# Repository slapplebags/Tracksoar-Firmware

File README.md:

## Tracksoar Firmware
==========
This is a modified version of the [trackduino](https://github.com/trackuino/trackuino) firmware for the [Tracksoar](www.tracksoar.com) hardware.

### Configuring Hardware Version
This branch uses a super basic HAL and as a result must be told what version of hardware it is running on. [Edit the config here](https://github.com/slapplebags/Tracksoar-Firmware/blob/BME280-support/Tracksoar/Firmware/tracksoar/config.h#L30) to have the corect version uncommented. Everything before V1.2 should work as it normally did on the old set of sensors.

#### Build Status

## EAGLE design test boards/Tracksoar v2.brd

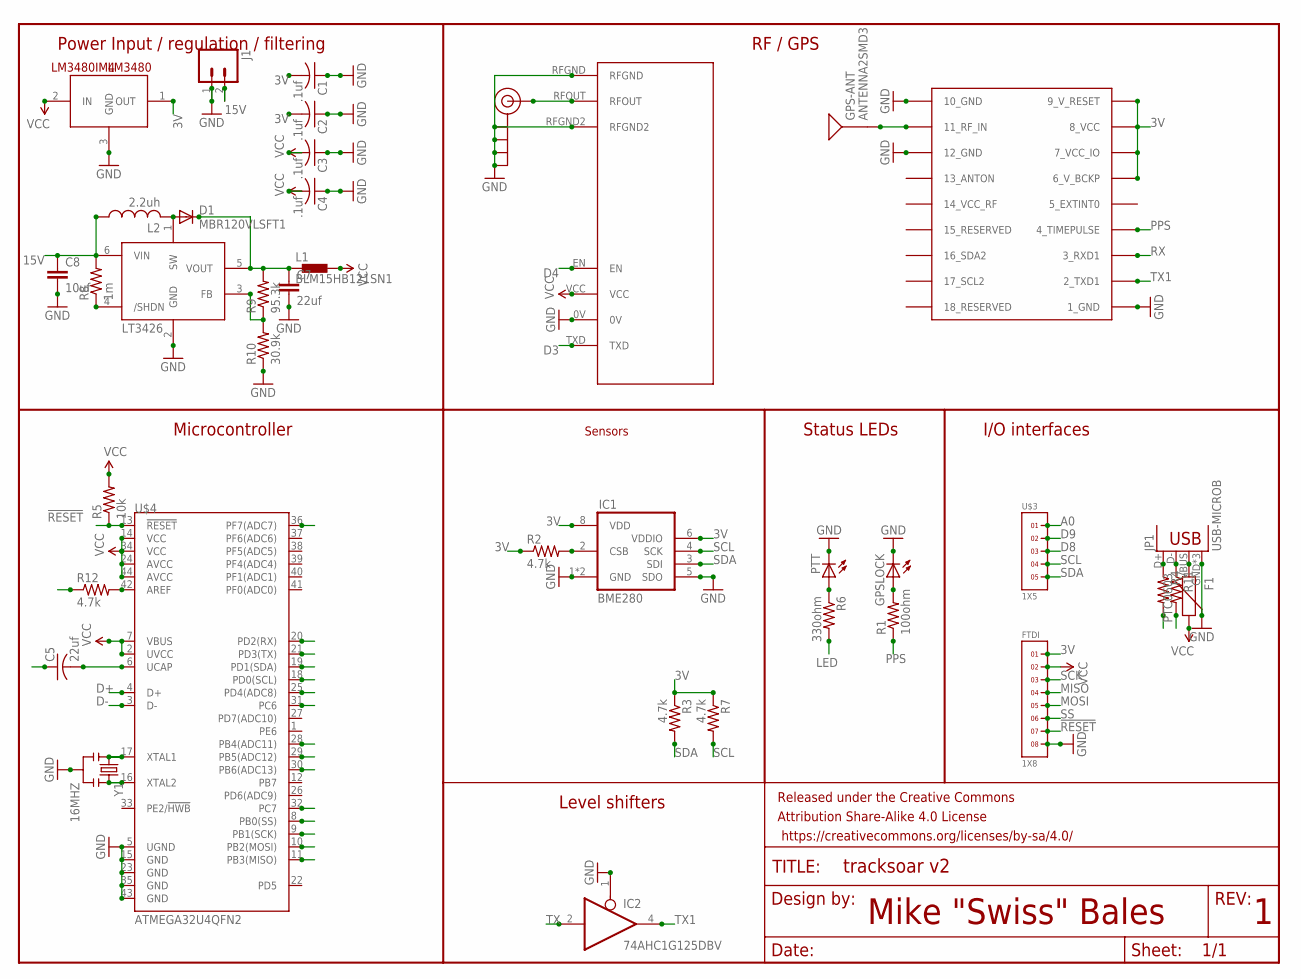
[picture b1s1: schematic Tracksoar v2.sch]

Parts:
C1, C2, C3, C4: .1uf; C0402
C5: 22uf; C0402
C7: 22uf; 0805
C8: 10uf; 0805
D1: MBR120VLSFT1; SOD123
F1: PTC0603; 0603
FRAME1: FRAME-LETTER; CREATIVE_COMMONS
FTDI: 1X8
GPS-ANT: ANTENNA2SMD3; ANTENNA-CHIP4
GPSLOCK: LEDCHIP-LED0603; CHIP-LED0603
IC1: BME280
IC2: 74AHC1G125DBV; SOT23-5
J1: M02JST-PTH-2; JST-2-PTH
J$1: SMA_EDGE; SMA-EDGE
JP1: USB-MICROB
L1: BLM15HB121SN1; 0402
L2: 2.2uh; L1812
LM3480: LM3480IM4; SOT23-3
LT3426: LT3426; SOT23-6
PTT: LEDCHIP-LED0603; CHIP-LED0603
R1: 100ohm; R0402
R2, R3, R7, R12: 4.7k; R0402
R4, R11: R-US_R0402; R0402
R5: 10k; R0402
R6: 330ohm; R0402
R8: 1m; R0402
R9: 95.3k; R0402
R10: 30.9k; R0402
U$1: UBLOX_MAX
U$2: RADIOMETRIX-HX1
U$3: 1X5
U$4: ATMEGA32U4QFN2; QFN-44-NOPAD
Y1: 16MHZ; RESONATOR-SMD

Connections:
3V: C1.2, C2.2, FTDI.1, IC1.6 (VDDIO), IC1.8 (VDD), LM3480.1 (OUT), R2.1, R3.1, R7.1, U$1.6_V_BCKP, U$1.7_VCC_IO, U$1.8_VCC, U$1.9_V_RESET
15V: C8.1, J1.2, L2.1, LT3426.6 (VIN), R8.2, R12.1
!RESET: FTDI.7, R5.1, U$4.13 (!RESET)
A0: U$3.1, U$4.36 (PF7(ADC7))
D3: U$2.TXD, U$4.30 (PB6(ADC13))
D4: U$2.EN, U$4.25 (PD4(ADC8))
D8: U$3.3, U$4.28 (PB4(ADC11))
D9: U$3.2, U$4.29 (PB5(ADC12))
D13: U$4.32 (PC7)
D+: R4.2, U$4.4 (D+)
D-: R11.2, U$4.3 (D-)
GND: C1.1, C2.1, C3.1, C4.1, C5.1, C7.2, C8.2, FTDI.8, GPSLOCK.C, IC1.1 (GND), IC1.5 (SDO), IC1.7 (GND), IC2.1 (OE), IC2.3 (GND), J1.1, J$1.GND@0 (GND), J$1.GND@1 (GND), J$1.GND@2 (GND), J$1.GND@3 (GND), JP1.GND, JP1.MT1 (GND), JP1.MT2 (GND), LM3480.3 (GND), LT3426.2 (GND), PTT.C, R10.1, U$1.1_GND, U$1.10_GND, U$1.12_GND, U$2.0V, U$2.RFGND, U$2.RFGND2, U$4.5 (UGND), U$4.15 (GND), U$4.23 (GND), U$4.35 (GND), U$4.43 (GND), Y1.2
LED: R6.2, U$4.31 (PC6)
MISO: FTDI.4, U$4.11 (PB3(MISO))
MOSI: FTDI.5, U$4.10 (PB2(MOSI))
unnamed: J$1.SIG (SIGNAL), U$2.RFOUT
unnamed: IC1.2 (CSB), R2.2
unnamed: GPSLOCK.A, R1.2
unnamed: GPS-ANT.SIG, U$1.11_RF_IN
unnamed: JP1.D-, R11.1
unnamed: JP1.D+, R4.1
unnamed: D1.A, L2.2, LT3426.1 (SW)
unnamed: LT3426.4 (/SHDN), R8.1
unnamed: LT3426.3 (FB), R9.1, R10.2
unnamed: F1.1, JP1.VBUS
unnamed: R12.2, U$4.42 (AREF)
unnamed: C7.1, D1.C, L1.1, LT3426.5 (VOUT), R9.2
unnamed: C5.2, U$4.6 (UCAP)
unnamed: PTT.A, R6.1
PPS: R1.1, U$1.4_TIMEPULSE
RX: U$1.3_RXD1, U$4.21 (PD3(TX))
SCK: FTDI.3, U$4.9 (PB1(SCK))
SCL: IC1.4 (SCK), R7.2, U$3.4, U$4.18 (PD0(SCL))
SDA: IC1.3 (SDI), R3.2, U$3.5, U$4.19 (PD1(SDA))
SS: FTDI.6, U$4.8 (PB0(SS))
TX: IC2.2 (I), U$4.20 (PD2(RX))
TX1: IC2.4 (O), U$1.2_TXD1
VCC: C3.2, C4.2, F1.2, FTDI.2, IC2.5 (VCC), L1.2, LM3480.2 (IN), R5.2, U$2.VCC, U$4.2 (UVCC), U$4.7 (VBUS), U$4.14 (VCC), U$4.24 (AVCC), U$4.34 (VCC), U$4.44 (AVCC)
XTAL1: U$4.17 (XTAL1), Y1.1
XTAL2: U$4.16 (XTAL2), Y1.3

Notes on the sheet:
Mike "Swiss" Bales
Power Input / regulation / filtering
RF / GPS
Microcontroller
Level shifters
Status LEDs
I/O interfaces
Sensors

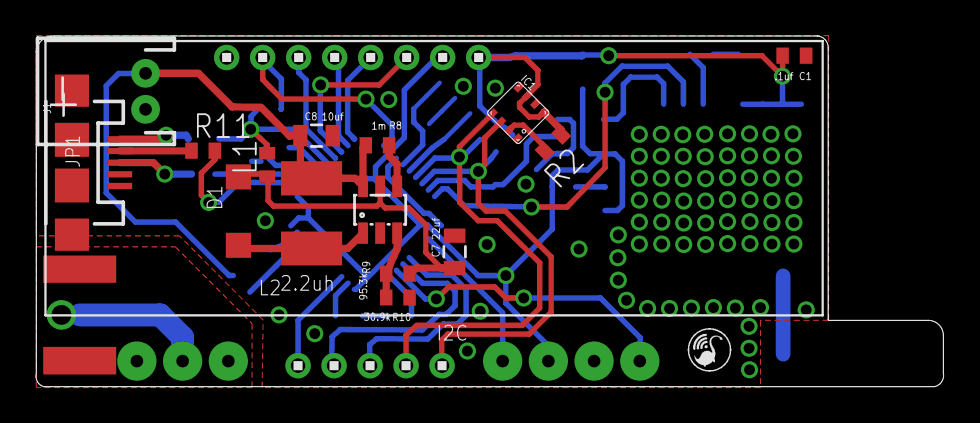
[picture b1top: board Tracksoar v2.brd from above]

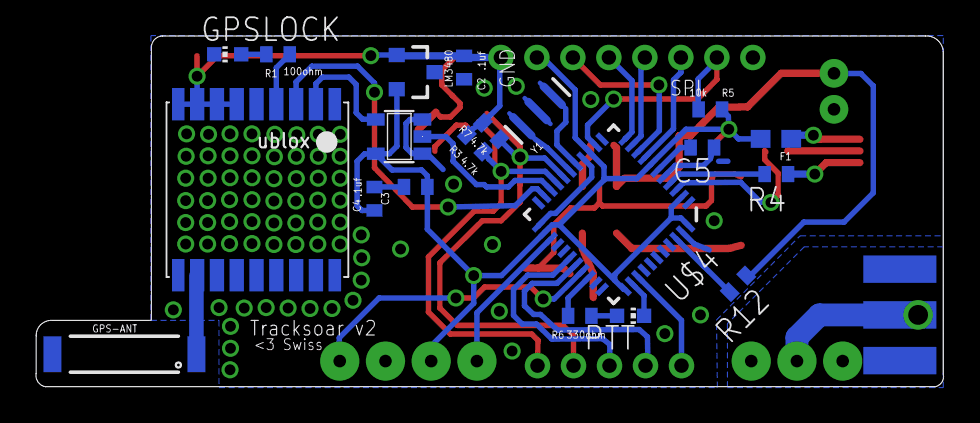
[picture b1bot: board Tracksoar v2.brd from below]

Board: 2 copper layers, 50.4 x 19.5 mm, 40 parts (21 on the bottom side), 39 nets.

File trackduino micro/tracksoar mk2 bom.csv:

"Part";"Value";"Device";"Package";"Description";"MPN";"OC_FARNELL";"OC_NEWARK";"PACKAGE";"PROD_ID";"SUPPLIER";"VALUE";
"BMP180";"BMP180";"BMP180";"BMP180";"BOSCH BMP180 DIGITAL BAROMETRIC PRESSURE SENSOR";"";"";"";"";"";"";"";
"C1";".1uf";"CAP0805";"0805";"Capacitor";"";"";"";"";"";"";"";
"C2";".1uf";"CAP0805";"0805";"Capacitor";"";"";"";"";"";"";"";
"C3";".1uf";"CAP0805";"0805";"Capacitor";"";"";"";"";"";"";"";
"C4";".1uf";"CAP0805";"0805";"Capacitor";"";"";"";"";"";"";"";
"C5";".1uf";"CAP0805";"0805";"Capacitor";"";"";"";"";"";"";"";
"C7";"22uf";"CAP0805";"0805";"Capacitor";"";"";"";"";"";"";"";
"C8";"10uf";"CAP0805";"0805";"Capacitor";"";"";"";"";"";"";"";
"C9";"100uf";"C-USC1206";"C1206";"CAPACITOR, American symbol";"";"";"";"";"";"";"";
"D1";"MBR120VLSFT1";"DIODE-SOD123";"SOD123";"DIODE";"";"";"";"";"";"";"";
"FRAME1";"FRAME-LETTER";"FRAME-LETTER";"CREATIVE_COMMONS";"Schematic Frame";"";"";"";"";"";"";"";
"FTDI";"";"M06NO_SILK_FEMALE_PTH";"1X06_NO_SILK";"Header 6";"";"";"";"";"CONN-08437";"";"";
"IC2";"74AHC1G125DBV";"74AHC1G125DBV";"SOT23-5";"Single Bus Buffer Gate with 3-State Output";"";"";"";"";"";"";"";
"J$1";"SMA_EDGE";"SMA_EDGE";"SMA-EDGE";"SMA Antenna Connector";"";"";"";"";"";"";"";
"JP1";"M02JST-PTH-VERT";"M02JST-PTH-VERT";"JST-2-PTH-VERT";"Standard 2-pin 0.1" header. Use with";"";"";"";"";"";"";"";
"L2";"2.2uh";"L-USL1812";"L1812";"INDUCTOR, American symbol";"";"";"";"";"";"";"";
"LED1";"";"LEDCHIP-LED0805";"CHIP-LED0805";"LED";"";"";"";"";"";"";"";
"LM3480";"LM3480IM4";"LM3480IM4";"SOT23-3";"Small package linear regulator";"";"";"";"";"";"";"";
"LT3426";"LT3426";"LT3426";"SOT23-6";"LT3426";"";"";"";"";"";"";"";
"PTT";"";"LEDCHIP-LED0805";"CHIP-LED0805";"LED";"";"";"";"";"";"";"";
"R1";"100ohm";"RESISTOR0805-RES";"0805";"Resistor";"";"";"";"";"";"";"";
"R3";"4.7k";"RESISTOR0805-RES";"0805";"Resistor";"";"";"";"";"";"";"";
"R5";"10k";"RESISTOR0805-RES";"0805";"Resistor";"";"";"";"";"";"";"";
"R6";"330ohm";"RESISTOR0805-RES";"0805";"Resistor";"";"";"";"";"";"";"";
"R7";"4.7k";"RESISTOR0805-RES";"0805";"Resistor";"";"";"";"";"";"";"";
"R8";"1m";"RESISTOR0805-RES";"0805";"Resistor";"";"";"";"";"";"";"";
"R9";"95.3k";"RESISTOR0805-RES";"0805";"Resistor";"";"";"";"";"";"";"";
"R10";"30.9k";"RESISTOR0805-RES";"0805";"Resistor";"";"";"";"";"";"";"";
"RX";"RX";"M02JST-PTH-VERT";"JST-2-PTH-VERT";"Standard 2-pin 0.1" header. Use with";"";"";"";"";"";"";"";
"SHT21";"SHT21";"SHT21";"DFN300X300X110-7N";"SENSOR, HUMIDITY & TEMP";"SHT21";"1855468";"20T1172";"DFN-6";"";"SENSIRION";"";
"SPI";"";"M04JST-PTH-VERT";"JST-4-PTH-VERT";"Header 4";"";"";"";"";"";"";"";
"SW1";"SPST_TACT-KMR2";"SPST_TACT-KMR2";"KMR2";"SMT 6mm switch, EVQQ2 series";"";"";"";"";"";"";"";
"TX";"TX";"M02JST-PTH-VERT";"JST-2-PTH-VERT";"Standard 2-pin 0.1" header. Use with";"";"";"";"";"";"";"";
"TX1";"TX";"M02JST-PTH-VERT";"JST-2-PTH-VERT";"Standard 2-pin 0.1" header. Use with";"";"";"";"";"";"";"";
"U$1";"UBLOX_MAX";"UBLOX_MAX";"UBLOX_MAX";"UBLOX MAX";"";"";"";"";"";"";"";
"U$2";"RADIOMETRIX-HX1";"RADIOMETRIX-HX1";"RADIOMETRIX-HX1";"";"";"";"";"";"";"";"";
"U$3";"ANTENNA2SMD3";"ANTENNA2SMD3";"ANTENNA-CHIP4";"Chip antenna";"";"";"";"";"";"";"";
"U1";"ATMEGA168MLF";"ATMEGA168MLF";"MLF32";"Atmel 32-pin 8-bit micro, 16k flash.";"";"";"";"";"";"";"";
"Y1";"16MHZ";"RESONATOR16MHZ";"RESONATOR-SMD";"Resonator";"";"";"";"";"XTAL-08900";"";"16MHZ";

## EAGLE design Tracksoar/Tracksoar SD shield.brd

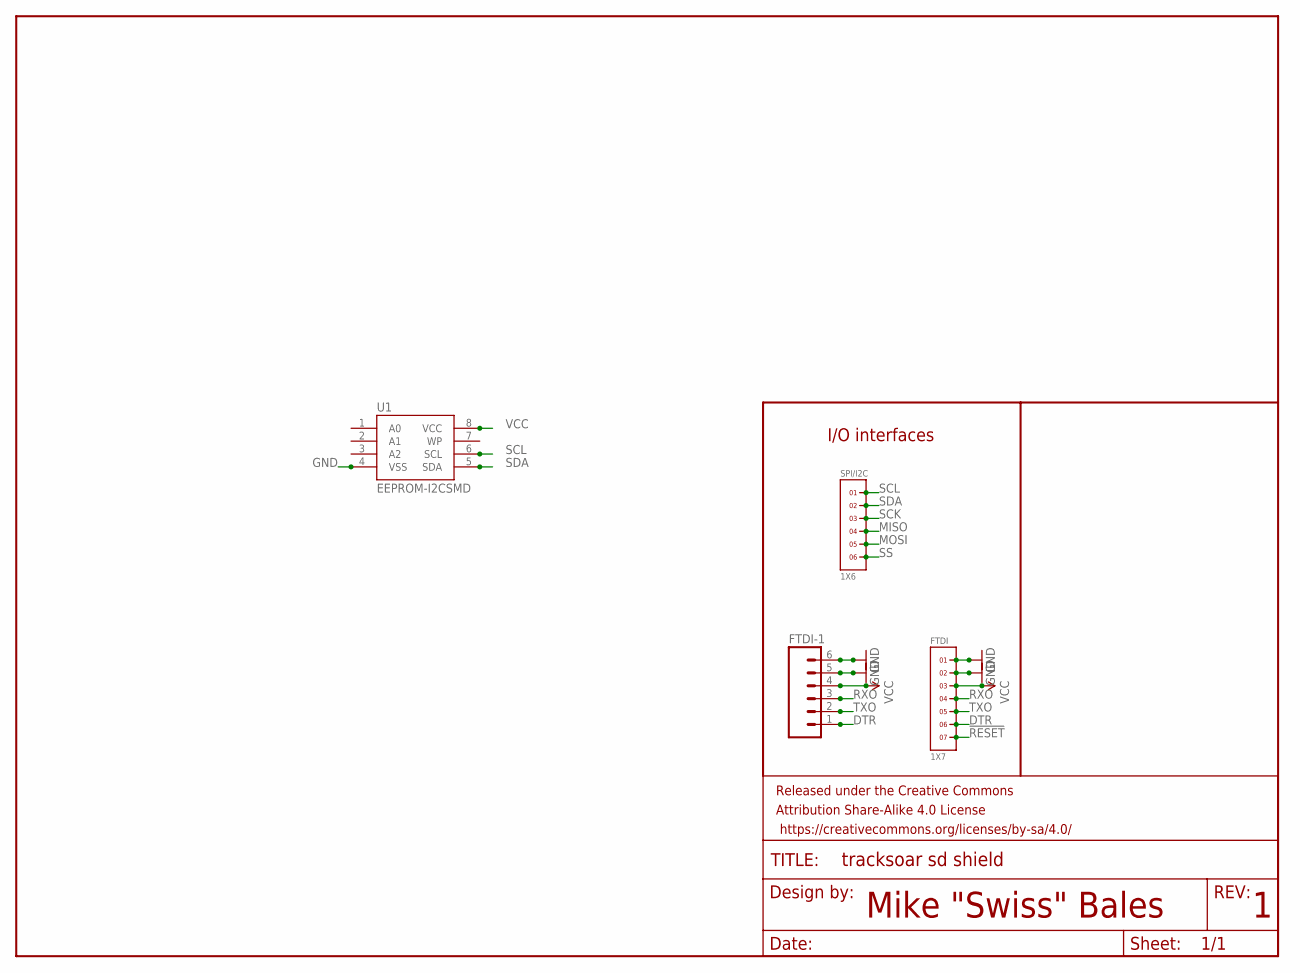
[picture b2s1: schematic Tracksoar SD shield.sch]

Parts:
FRAME1: FRAME-LETTER; CREATIVE_COMMONS
FTDI: 1X7
FTDI-1: M06LOCK_LONGPADS; 1X06_LOCK_LONGPADS
SPI/I2C: 1X6
U1: EEPROM-I2CSMD; SO08

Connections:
!RESET: FTDI.7
DTR: FTDI.6, FTDI-1.1
GND: FTDI.1, FTDI.2, FTDI-1.5, FTDI-1.6, U1.4 (VSS)
MISO: SPI/I2C.4
MOSI: SPI/I2C.5
RXO: FTDI.4, FTDI-1.3
SCK: SPI/I2C.3
SCL: SPI/I2C.1, U1.6 (SCL)
SDA: SPI/I2C.2, U1.5 (SDA)
SS: SPI/I2C.6
TXO: FTDI.5, FTDI-1.2
VCC: FTDI.3, FTDI-1.4, U1.8 (VCC)

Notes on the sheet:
Mike "Swiss" Bales
I/O interfaces

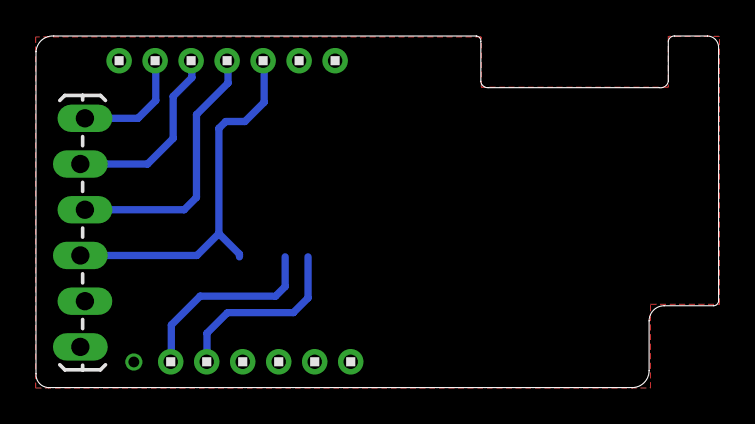
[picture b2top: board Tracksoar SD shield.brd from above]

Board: 2 copper layers, 37.9 x 19.5 mm, 5 parts (1 on the bottom side), 7 nets.

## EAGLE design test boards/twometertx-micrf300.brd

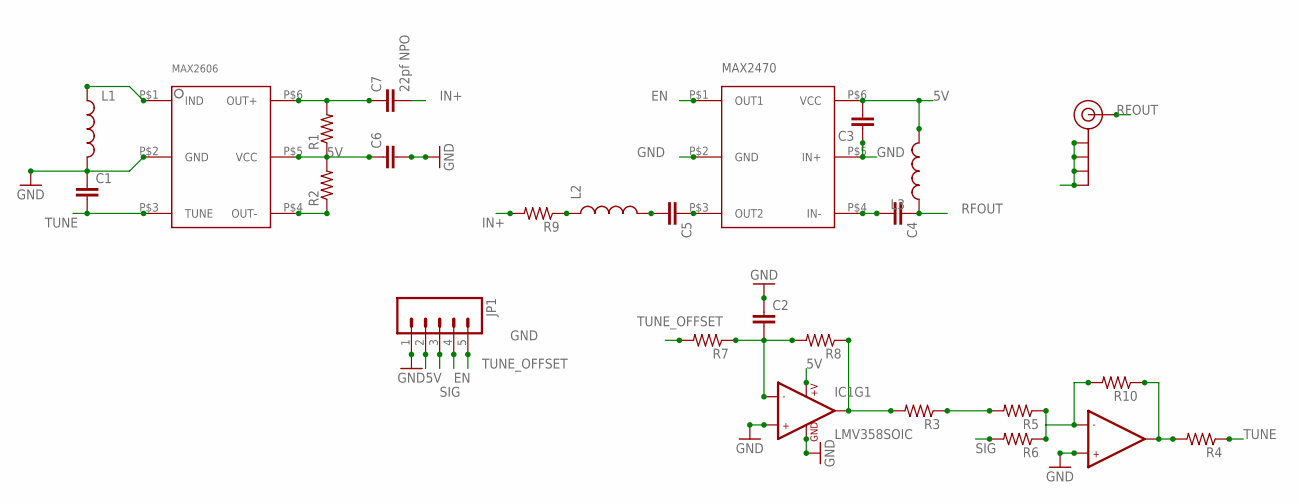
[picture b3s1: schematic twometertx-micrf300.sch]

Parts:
C1, C2, C3, C4, C5, C6: CAP0805; 0805
C7: 22pf NPO; 0805
IC1: LMV358SOIC; SO08
J$1: SMA_EDGE; SMA-EDGE
JP1: M05PTH_LONGPADS; 1X05_LONGPADS
L1, L2, L3: INDUCTOR0805; 0805
R1, R2, R3, R4, R5, R6, R7, R8, R9, R10: RESISTOR0805-RES; 0805
U$1: MAX2606
U$2: MAX2470

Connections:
5V: C3.2, C6.1, IC1.8 (+V), JP1.2, L3.2, R1.1, R2.2, U$1.P$5 (VCC), U$2.P$6 (VCC)
EN: JP1.4, U$2.P$1 (OUT1)
GND: C1.1, C2.1, C3.1, C4.2, C6.2, IC1.3 (+IN1), IC1.4 (GND), IC1.5 (+IN2), J$1.GND@0 (GND), J$1.GND@1 (GND), J$1.GND@2 (GND), J$1.GND@3 (GND), JP1.1, L1.2, U$1.P$2 (GND), U$2.P$2 (GND), U$2.P$4 (IN-), U$2.P$5 (IN+)
IN+: C7.2, R9.2
unnamed: C5.1, U$2.P$3 (OUT2)
unnamed: L1.1, U$1.P$1 (IND)
unnamed: C2.2, IC1.2 (-IN1), R7.1, R8.2
unnamed: C5.2, L2.2
unnamed: R3.1, R5.2
unnamed: IC1.7 (OUT2), R4.2, R10.1
unnamed: IC1.6 (-IN2), R5.1, R6.1, R10.2
unnamed: L2.1, R9.1
unnamed: C7.1, R1.2, U$1.P$6 (OUT+)
unnamed: IC1.1 (OUT1), R3.2, R8.1
RFOUT: C4.1, J$1.SIG (SIGNAL), L3.1
SIG: JP1.3, R6.2
THING2: R2.1, U$1.P$4 (OUT-)
TUNE: C1.2, R4.1, U$1.P$3 (TUNE)
TUNE_OFFSET: JP1.5, R7.2

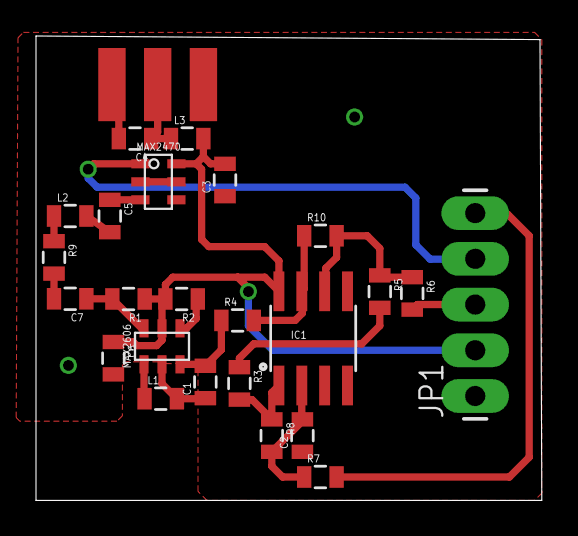
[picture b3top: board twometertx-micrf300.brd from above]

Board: 2 copper layers, 28.1 x 25.8 mm, 25 parts (0 on the bottom side), 19 nets.

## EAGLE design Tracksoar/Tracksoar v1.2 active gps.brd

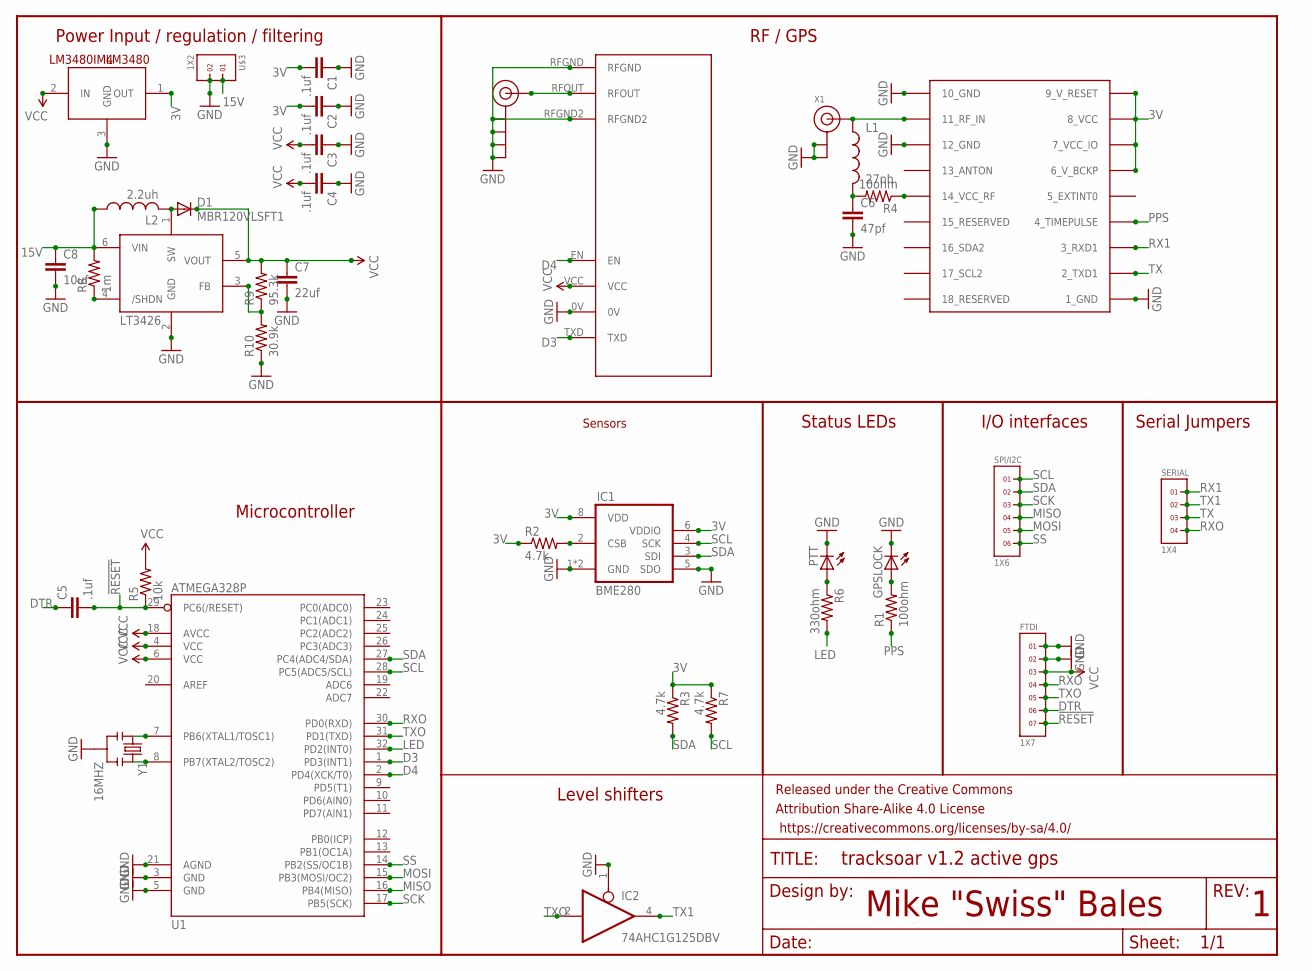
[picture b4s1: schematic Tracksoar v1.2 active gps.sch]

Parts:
C1, C2, C3, C4, C5: .1uf; 0805
C6: 47pf; 0805
C7: 22uf; 0805
C8: 10uf; 0805
D1: MBR120VLSFT1; SOD123
FRAME1: FRAME-LETTER; CREATIVE_COMMONS
FTDI: 1X7
GPSLOCK: LEDCHIP-LED0805; CHIP-LED0805
IC1: BME280
IC2: 74AHC1G125DBV; SOT23-5
J$1: SMA_EDGE; SMA-EDGE
L1: 27nh; 0805
L2: 2.2uh; L1812
LM3480: LM3480IM4; SOT23-3
LT3426: LT3426; SOT23-6
PTT: LEDCHIP-LED0805; CHIP-LED0805
R1: 100ohm; 0805
R2, R3, R7: 4.7k; 0805
R4: 10ohm; 0805
R5: 10k; 0805
R6: 330ohm; 0805
R8: 1m; 0805
R9: 95.3k; 0805
R10: 30.9k; 0805
SERIAL: 1X4
SPI/I2C: 1X6
U1: ATMEGA328P; MLF32
U$1: UBLOX_MAX
U$2: RADIOMETRIX-HX1
U$3: 1X2
X1: ANTENNA_U.FL; U.FL
Y1: 16MHZ; RESONATOR-SMD

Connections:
3V: C1.2, C2.2, IC1.6 (VDDIO), IC1.8 (VDD), LM3480.1 (OUT), R2.1, R3.1, R7.1, U$1.6_V_BCKP, U$1.7_VCC_IO, U$1.8_VCC, U$1.9_V_RESET
15V: C8.1, L2.1, LT3426.6 (VIN), R8.2, U$3.1
!RESET: C5.2, FTDI.7, R5.1, U1.29 (PC6(/RESET))
D3: U1.1 (PD3(INT1)), U$2.TXD
D4: U1.2 (PD4(XCK/T0)), U$2.EN
DTR: C5.1, FTDI.6
GND: C1.1, C2.1, C3.1, C4.1, C6.2, C7.2, C8.2, FTDI.1, FTDI.2, GPSLOCK.C, IC1.1 (GND), IC1.5 (SDO), IC1.7 (GND), IC2.1 (OE), IC2.3 (GND), J$1.GND@0 (GND), J$1.GND@1 (GND), J$1.GND@2 (GND), J$1.GND@3 (GND), LM3480.3 (GND), LT3426.2 (GND), PTT.C, R10.1, U1.3 (GND), U1.5 (GND), U1.21 (AGND), U$1.1_GND, U$1.10_GND, U$1.12_GND, U$2.0V, U$2.RFGND, U$2.RFGND2, U$3.2, X1.1 (GND), X1.2 (GND), Y1.2
LED: R6.2, U1.32 (PD2(INT0))
MISO: SPI/I2C.4, U1.16 (PB4(MISO))
MOSI: SPI/I2C.5, U1.15 (PB3(MOSI/OC2))
unnamed: J$1.SIG (SIGNAL), U$2.RFOUT
unnamed: IC1.2 (CSB), R2.2
unnamed: GPSLOCK.A, R1.2
unnamed: L1.1, U$1.11_RF_IN, X1.3 (SIGNAL)
unnamed: C6.1, L1.2, R4.2
unnamed: R4.1, U$1.14_VCC_RF
unnamed: D1.A, L2.2, LT3426.1 (SW)
unnamed: LT3426.4 (/SHDN), R8.1
unnamed: LT3426.3 (FB), R9.1, R10.2
unnamed: U1.8 (PB7(XTAL2/TOSC2)), Y1.3
unnamed: U1.7 (PB6(XTAL1/TOSC1)), Y1.1
unnamed: PTT.A, R6.1
PPS: R1.1, U$1.4_TIMEPULSE
RX1: SERIAL.1, U$1.3_RXD1
RXO: FTDI.4, SERIAL.4, U1.30 (PD0(RXD))
SCK: SPI/I2C.3, U1.17 (PB5(SCK))
SCL: IC1.4 (SCK), R7.2, SPI/I2C.1, U1.28 (PC5(ADC5/SCL))
SDA: IC1.3 (SDI), R3.2, SPI/I2C.2, U1.27 (PC4(ADC4/SDA))
SS: SPI/I2C.6, U1.14 (PB2(SS/OC1B))
TX: SERIAL.3, U$1.2_TXD1
TX1: IC2.4 (O), SERIAL.2
TXO: FTDI.5, IC2.2 (I), U1.31 (PD1(TXD))
VCC: C3.2, C4.2, C7.1, D1.C, FTDI.3, IC2.5 (VCC), LM3480.2 (IN), LT3426.5 (VOUT), R5.2, R9.2, U1.4 (VCC), U1.6 (VCC), U1.18 (AVCC), U$2.VCC

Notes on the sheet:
Mike "Swiss" Bales
Power Input / regulation / filtering
RF / GPS
Microcontroller
Level shifters
Status LEDs
I/O interfaces
Serial Jumpers
Sensors

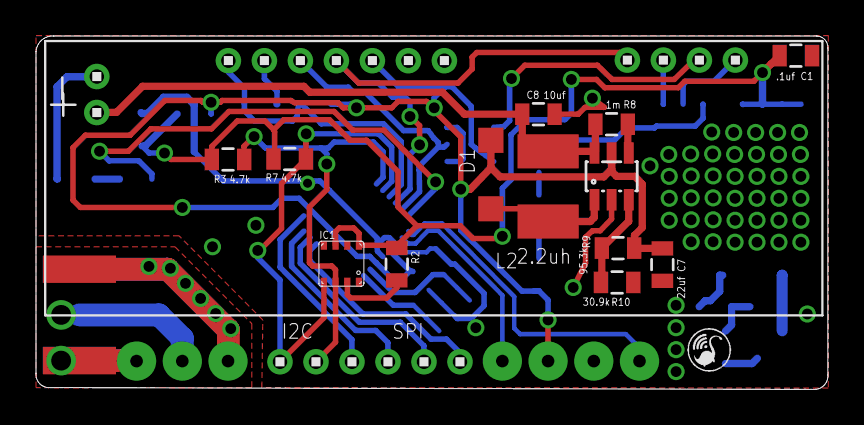
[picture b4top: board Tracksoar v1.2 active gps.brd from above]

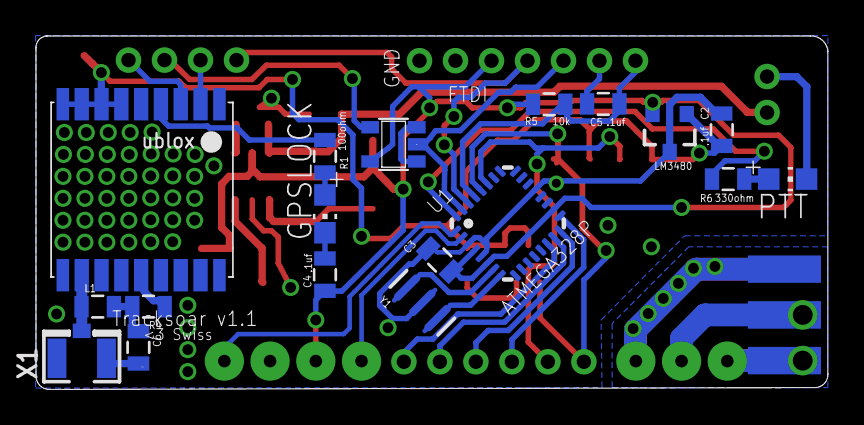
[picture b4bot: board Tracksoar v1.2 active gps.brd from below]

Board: 2 copper layers, 44.0 x 19.6 mm, 38 parts (19 on the bottom side), 33 nets.

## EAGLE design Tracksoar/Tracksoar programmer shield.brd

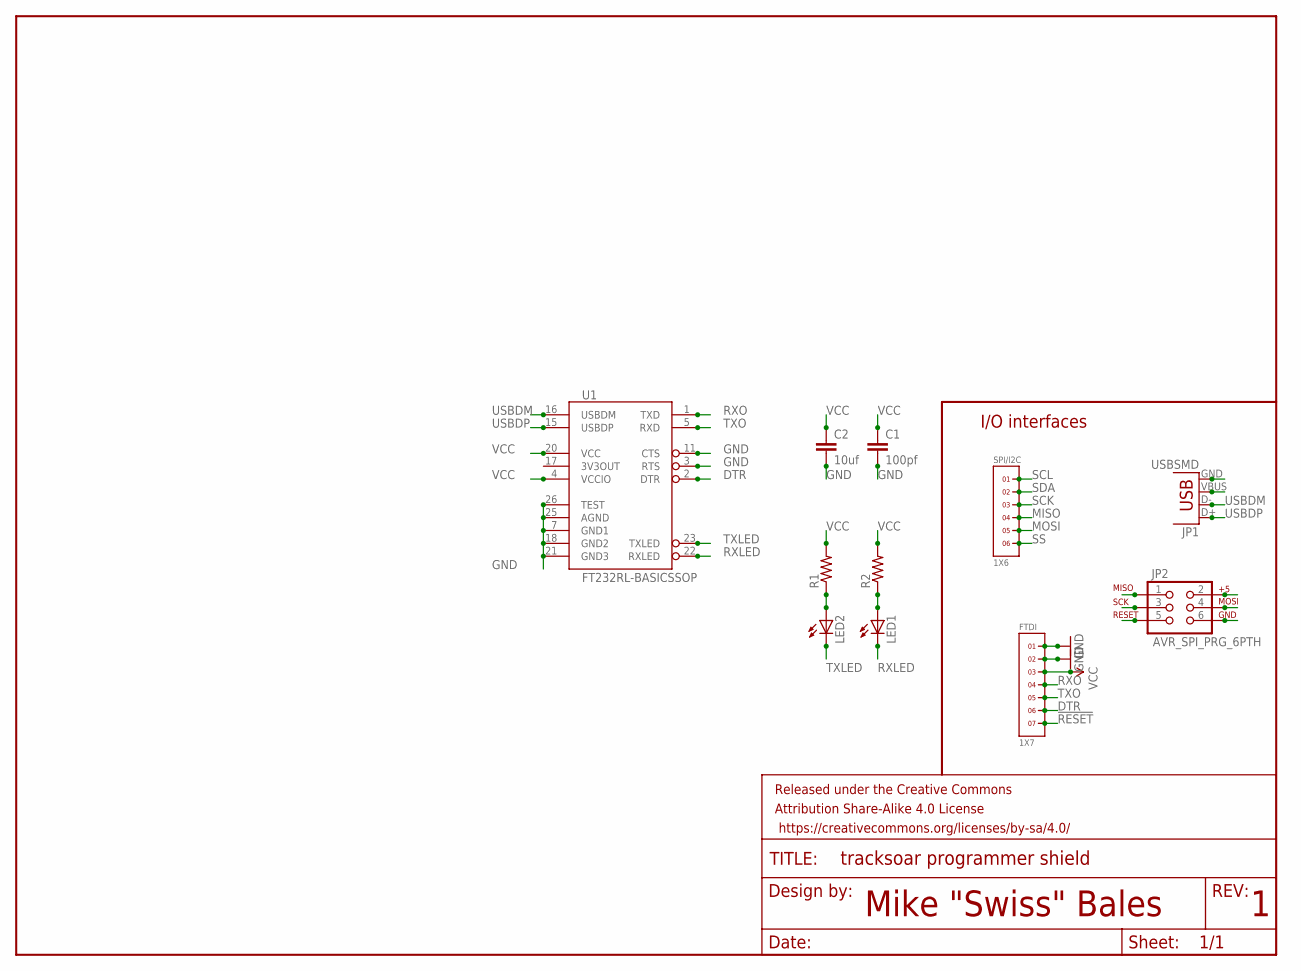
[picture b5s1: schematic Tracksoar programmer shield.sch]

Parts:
C1: 100pf; 0805
C2: 10uf; 0805
FRAME1: FRAME-LETTER; CREATIVE_COMMONS
FTDI: 1X7
JP1: USBSMD; USB-MINIB
JP2: AVR_SPI_PRG_6PTH; 2X3
LED1, LED2: LEDCHIP-LED0805; CHIP-LED0805
R1, R2: RESISTOR0805-RES; 0805
SPI/I2C: 1X6
U1: FT232RL-BASICSSOP; SSOP28DB

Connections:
!RESET: FTDI.7, JP2.5
DTR: FTDI.6, U1.2 (DTR)
GND: C1.2, C2.2, FTDI.1, FTDI.2, JP1.GND, JP2.6, U1.3 (RTS), U1.7 (GND1), U1.11 (CTS), U1.18 (GND2), U1.21 (GND3), U1.25 (AGND), U1.26 (TEST)
MISO: JP2.1, SPI/I2C.4
MOSI: JP2.4, SPI/I2C.5
unnamed: LED2.A, R1.1
unnamed: LED1.A, R2.1
RXLED: LED1.C, U1.22 (RXLED)
RXO: FTDI.4, U1.1 (TXD)
SCK: JP2.3, SPI/I2C.3
SCL: SPI/I2C.1
SDA: SPI/I2C.2
SS: SPI/I2C.6
TXLED: LED2.C, U1.23 (TXLED)
TXO: FTDI.5, U1.5 (RXD)
USBDM: JP1.D-, U1.16 (USBDM)
USBDP: JP1.D+, U1.15 (USBDP)
VCC: C1.1, C2.1, FTDI.3, JP1.VBUS, JP2.2, R1.2, R2.2, U1.4 (VCCIO), U1.20 (VCC)

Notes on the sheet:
Mike "Swiss" Bales
I/O interfaces

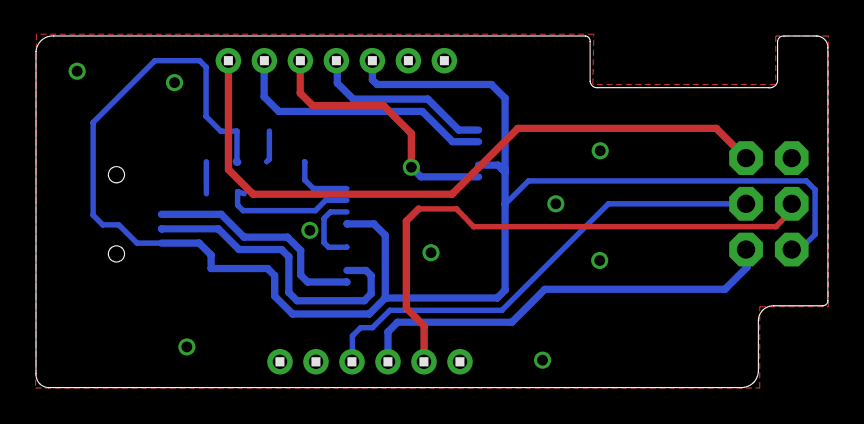
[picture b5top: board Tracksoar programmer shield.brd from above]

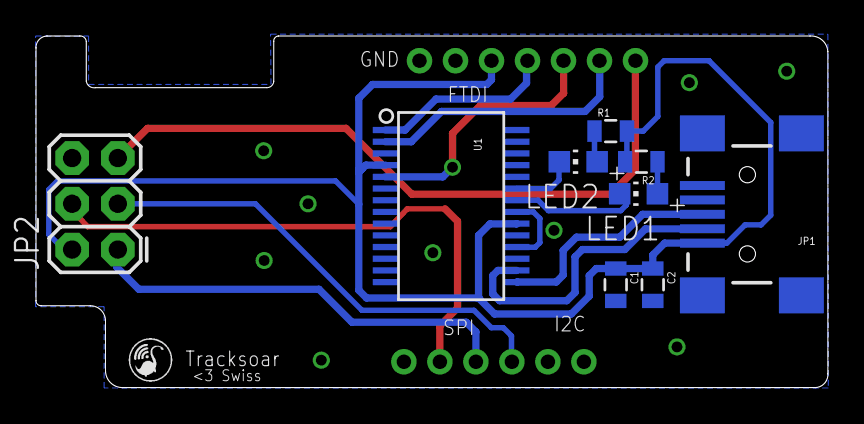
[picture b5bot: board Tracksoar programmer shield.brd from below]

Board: 2 copper layers, 44.0 x 19.5 mm, 12 parts (9 on the bottom side), 15 nets.

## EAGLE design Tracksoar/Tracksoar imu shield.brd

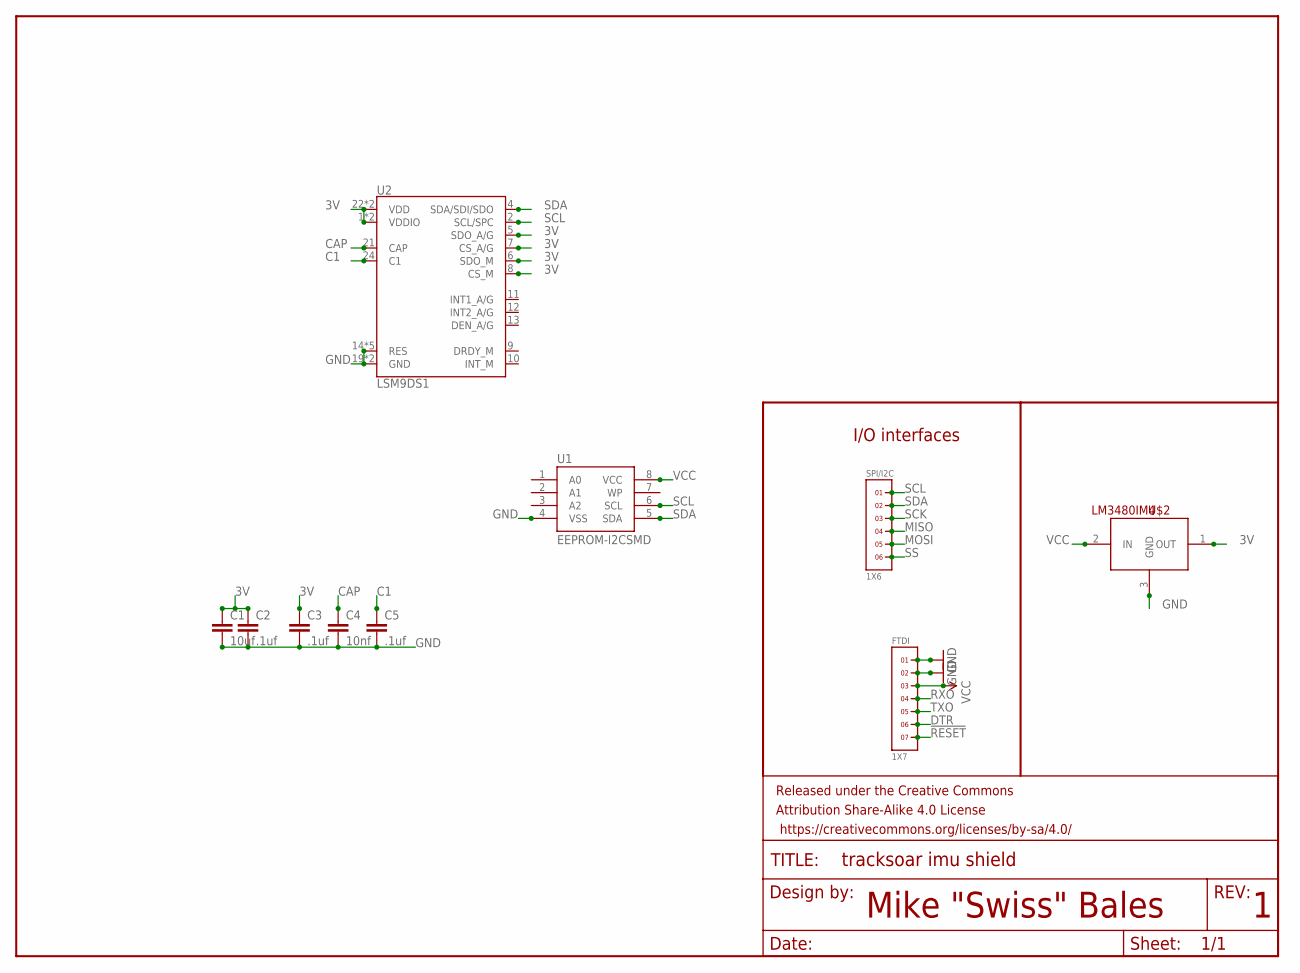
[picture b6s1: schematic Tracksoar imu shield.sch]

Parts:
C1: 10uf; 0805
C2, C3, C5: .1uf; 0805
C4: 10nf; 0805
FRAME1: FRAME-LETTER; CREATIVE_COMMONS
FTDI: 1X7
SPI/I2C: 1X6
U1: EEPROM-I2CSMD; SO08
U2: LSM9DS1; LGA24-8X4
U$2: LM3480IM4; SOT23-3

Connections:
3V: C1.1, C2.1, C3.1, U2.1 (VDDIO), U2.3 (VDDIO), U2.5 (SDO_A/G), U2.6 (SDO_M), U2.7 (CS_A/G), U2.8 (CS_M), U2.22 (VDD), U2.23 (VDD), U$2.1 (OUT)
!RESET: FTDI.7
C1: C5.1, U2.24 (C1)
CAP: C4.1, U2.21 (CAP)
DTR: FTDI.6
GND: C1.2, C2.2, C3.2, C4.2, C5.2, FTDI.1, FTDI.2, U1.4 (VSS), U2.14 (RES), U2.15 (RES), U2.16 (RES), U2.17 (RES), U2.18 (RES), U2.19 (GND), U2.20 (GND), U$2.3 (GND)
MISO: SPI/I2C.4
MOSI: SPI/I2C.5
RXO: FTDI.4
SCK: SPI/I2C.3
SCL: SPI/I2C.1, U1.6 (SCL), U2.2 (SCL/SPC)
SDA: SPI/I2C.2, U1.5 (SDA), U2.4 (SDA/SDI/SDO)
SS: SPI/I2C.6
TXO: FTDI.5
VCC: FTDI.3, U1.8 (VCC), U$2.2 (IN)

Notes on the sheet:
Mike "Swiss" Bales
I/O interfaces

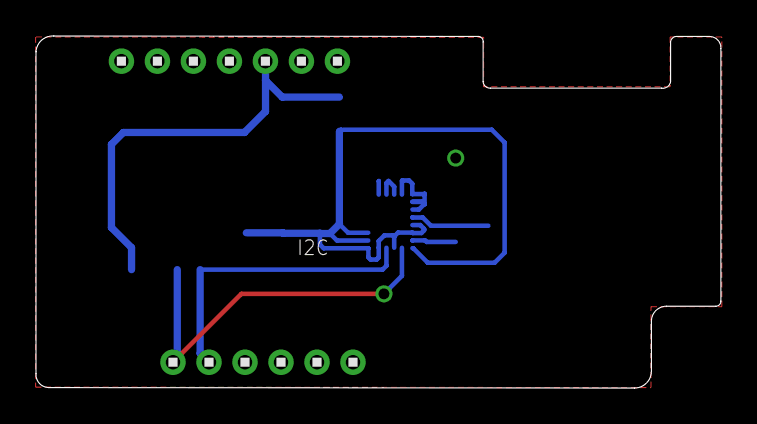
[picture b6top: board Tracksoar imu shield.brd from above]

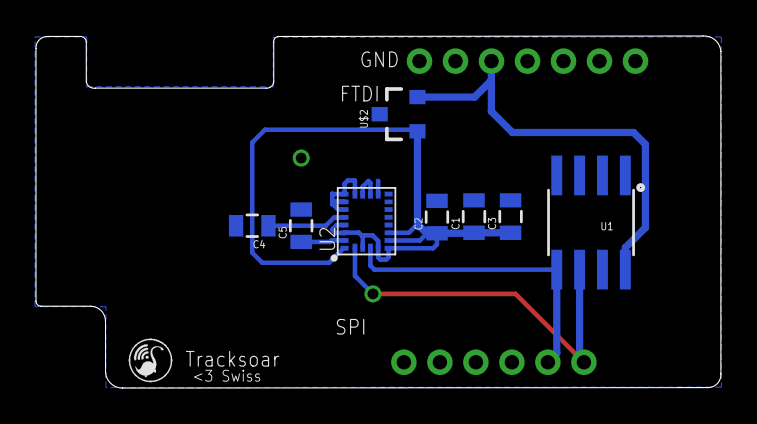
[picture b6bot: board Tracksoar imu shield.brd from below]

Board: 2 copper layers, 38.0 x 19.6 mm, 11 parts (8 on the bottom side), 7 nets.

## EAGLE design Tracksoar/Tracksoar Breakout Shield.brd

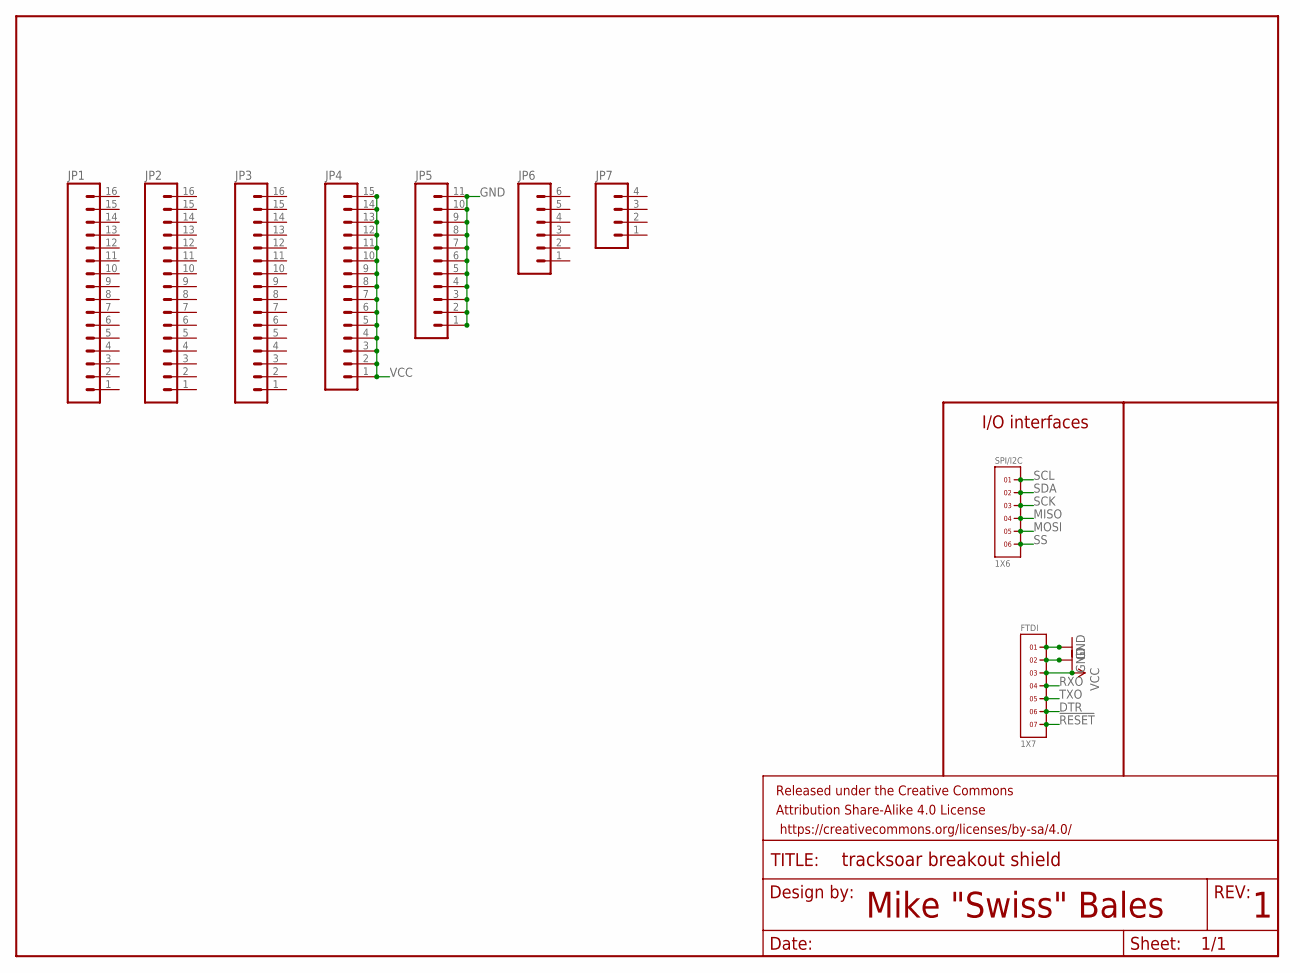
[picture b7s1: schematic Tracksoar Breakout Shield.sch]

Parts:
FRAME1: FRAME-LETTER; CREATIVE_COMMONS
FTDI: 1X7
JP1, JP2, JP3: M161X16_NO_SILK; 1X16_NO_SILK
JP4: M15; 1X15
JP5: M11PTH; 1X11
JP6: M06NO_SILK_FEMALE_PTH; 1X06_NO_SILK
JP7: M04NO_SILK_ALL_ROUND; 1X04_NO_SILK_ALL_ROUND
SPI/I2C: 1X6

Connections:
!RESET: FTDI.7
DTR: FTDI.6
GND: FTDI.1, FTDI.2, JP5.1, JP5.2, JP5.3, JP5.4, JP5.5, JP5.6, JP5.7, JP5.8, JP5.9, JP5.10, JP5.11
MISO: SPI/I2C.4
MOSI: SPI/I2C.5
RXO: FTDI.4
SCK: SPI/I2C.3
SCL: SPI/I2C.1
SDA: SPI/I2C.2
SS: SPI/I2C.6
TXO: FTDI.5
VCC: FTDI.3, JP4.1, JP4.2, JP4.3, JP4.4, JP4.5, JP4.6, JP4.7, JP4.8, JP4.9, JP4.10, JP4.11, JP4.12, JP4.13, JP4.14, JP4.15

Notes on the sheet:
Mike "Swiss" Bales
I/O interfaces

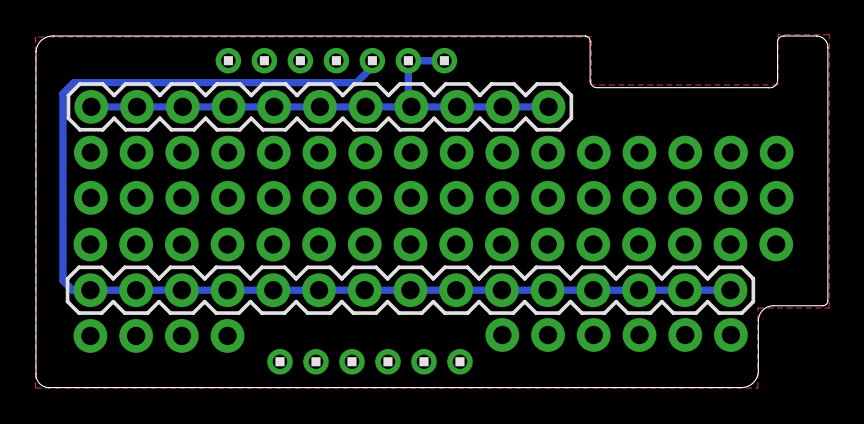
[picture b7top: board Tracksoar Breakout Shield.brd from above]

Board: 2 copper layers, 44.0 x 19.5 mm, 10 parts (0 on the bottom side), 2 nets.

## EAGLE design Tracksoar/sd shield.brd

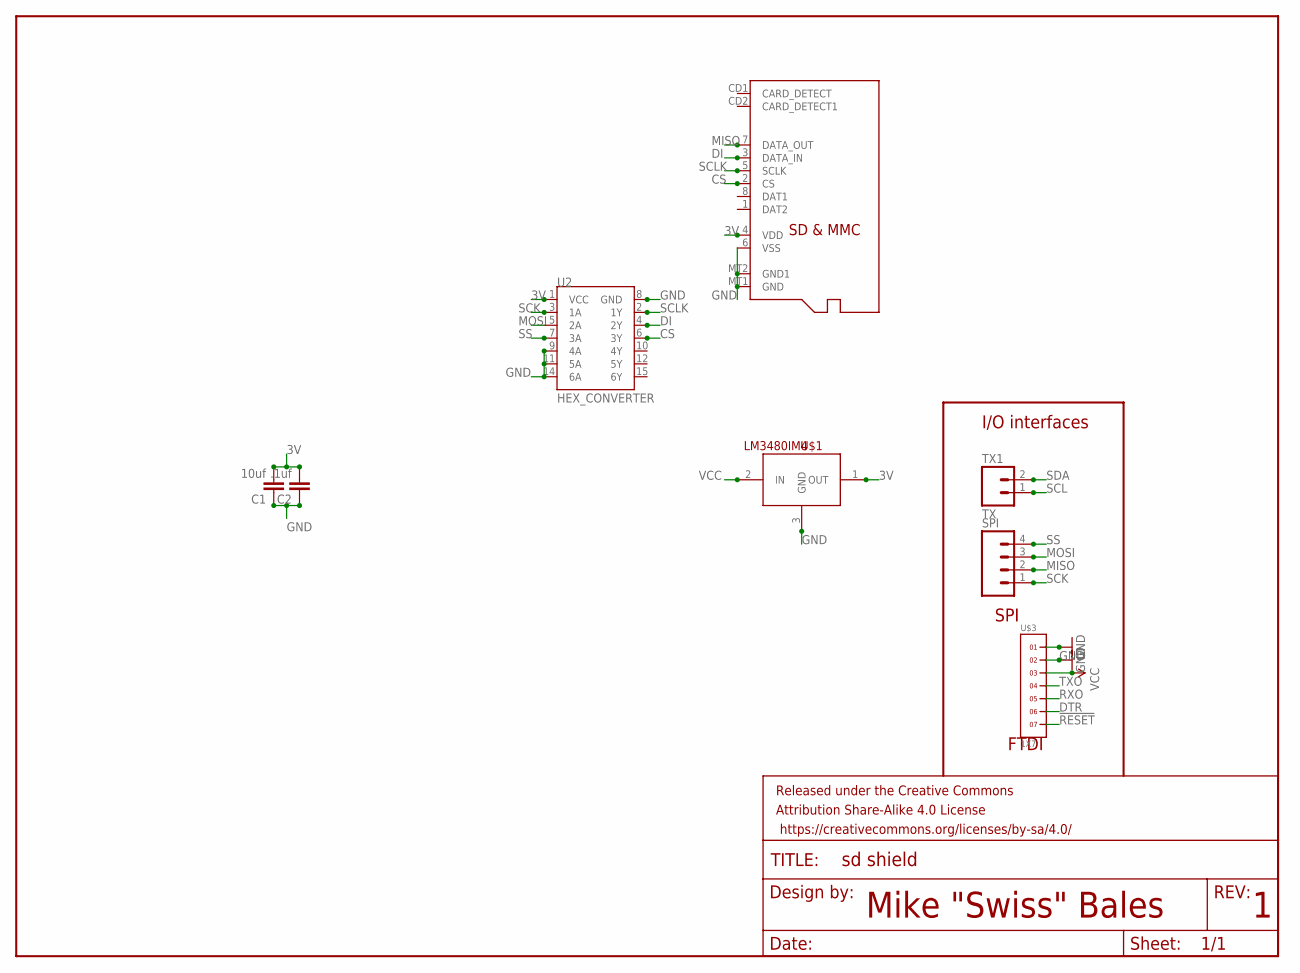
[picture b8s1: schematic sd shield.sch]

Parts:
C1: 10uf; 0805
C2: .1uf; 0805
FRAME1: FRAME-LETTER; CREATIVE_COMMONS
SPI: M04JST-PTH-VERT; JST-4-PTH-VERT
TX1: TX; JST-2-PTH-VERT
U2: HEX_CONVERTER; SO016
U$1: LM3480IM4; SOT23-3
U$2: MICROSD
U$3: 1X7

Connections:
3V: C1.2, C2.2, U2.1 (VCC), U$1.1 (OUT), U$2.4 (VDD)
!RESET: U$3.7
CS: U2.6 (3Y), U$2.2 (CS)
DI: U2.4 (2Y), U$2.3 (DATA_IN)
DTR: U$3.6
GND: C1.1, C2.1, U2.8 (GND), U2.9 (4A), U2.11 (5A), U2.14 (6A), U$1.3 (GND), U$2.6 (VSS), U$2.MT1 (GND), U$2.MT2 (GND1), U$3.1, U$3.2
MISO: SPI.2, U$2.7 (DATA_OUT)
MOSI: SPI.3, U2.5 (2A)
RXO: U$3.5
SCK: SPI.1, U2.3 (1A)
SCL: TX1.1
SCLK: U2.2 (1Y), U$2.5 (SCLK)
SDA: TX1.2
SS: SPI.4, U2.7 (3A)
TXO: U$3.4
VCC: U$1.2 (IN), U$3.3

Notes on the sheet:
Mike "Swiss" Bales
I/O interfaces
SPI
FTDI

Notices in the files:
parts and their libraries:
SparkFun-Aesthetics: Licensing: Creative Commons ShareAlike 4.0 International - https://creativecommons.org/licenses/by-sa/4.0
SparkFun-Aesthetics: Released under the Creative Commons Attribution Share-Alike 4.0 License
SparkFun-Aesthetics: https://creativecommons.org/licenses/by-sa/4.0
